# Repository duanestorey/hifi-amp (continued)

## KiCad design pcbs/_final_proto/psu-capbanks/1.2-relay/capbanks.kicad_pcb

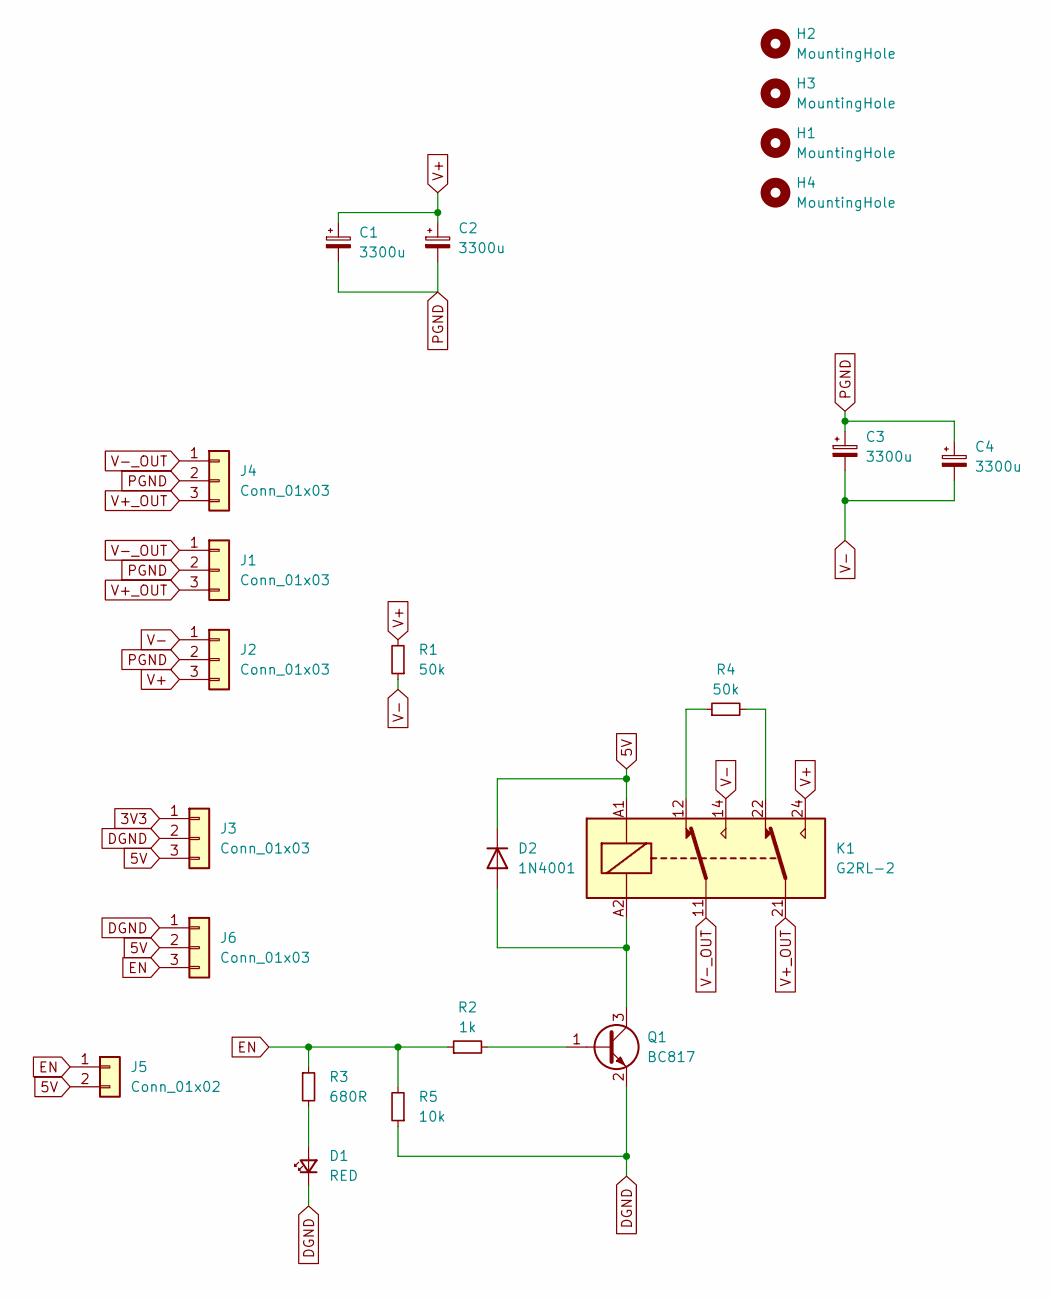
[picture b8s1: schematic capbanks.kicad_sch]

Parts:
C1, C2, C3, C4: 3300u; CP_Radial_D16.0mm_P7.50mm
D1: RED; LED_0805_2012Metric_Pad_HandSolder_Duane
D2: 1N4001; D_SMA
H1, H2, H3, H4: MountingHole; MountingHole_3.2mm_M3_DIN965_Pad_TopBottom
J1, J2, J4: Conn_01x03; JST_VH_B3P-VH-B_1x03_P3.96mm_Vertical_Duane
J3, J6: Conn_01x03; JST_PH_B3B-PH-K_1x03_P2.00mm_Vertical
J5: Conn_01x02; PinHeader_1x02_P2.54mm_Vertical
K1: G2RL-2; Relay_DPDT_Omron_G2RL-2
Q1: BC817; SOT-23
R1, R4: 50k; R_0805_2012Metric_Pad1.20x1.40mm_HandSolder_Duane
R2: 1k; R_0805_2012Metric_Pad1.20x1.40mm_HandSolder_Duane
R3: 680R; R_0805_2012Metric_Pad1.20x1.40mm_HandSolder_Duane
R5: 10k; R_0805_2012Metric_Pad1.20x1.40mm_HandSolder_Duane

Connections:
3V3: J3.1
5V: D2.1 (K), J3.3, J5.2, J6.2, K1.A1
DGND: D1.1 (K), J3.2, J6.1, Q1.2 (E), R5.1
EN: J5.1, J6.3, R2.1, R3.1, R5.2
unnamed: D1.2 (A), R3.2
unnamed: D2.2 (A), K1.A2, Q1.3 (C)
unnamed: K1.12, R4.1
unnamed: K1.22, R4.2
unnamed: Q1.1 (B), R2.2
PGND: C1.2, C2.2, C3.1, C4.1, J1.2, J2.2, J4.2
V+: C1.1, C2.1, J2.3, K1.24, R1.2
V+_OUT: J1.3, J4.3, K1.21
V-: C3.2, C4.2, J2.1, K1.14, R1.1
V-_OUT: J1.1, J4.1, K1.11

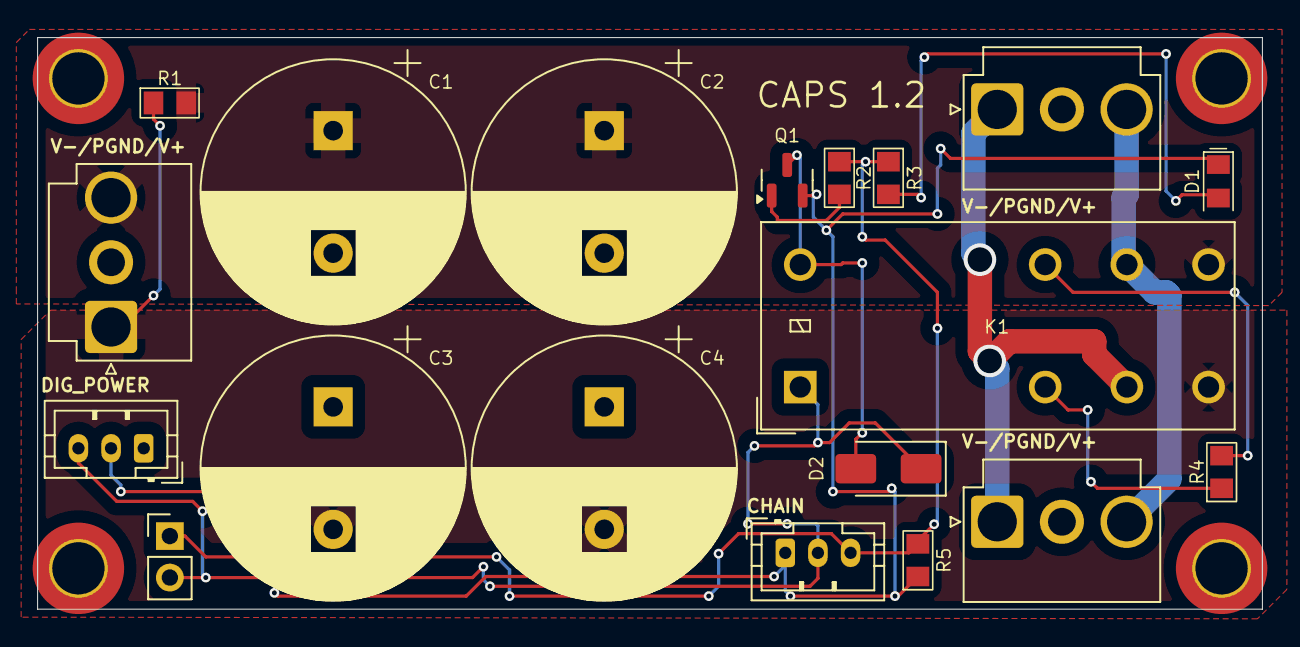
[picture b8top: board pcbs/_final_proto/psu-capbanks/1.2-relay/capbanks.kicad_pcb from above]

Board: 2 copper layers, 75.0 x 35.0 mm, 23 parts (0 on the bottom side), 13 nets.

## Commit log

2025-01-05 Adding submodules
2025-01-05 Adding license
2025-01-12 Create CNAME
2025-01-12 Fixes
2025-01-13 Display
2025-01-13 Adding
2025-01-13 Vinyl
2025-01-13 Adding dsp
2025-01-13 Cahnge for text
2025-01-13 Adding dual psu
2025-01-13 Updating extend
2025-01-13 Adding spdif
2025-01-13 input sel
2025-01-13 lm3886
2025-01-13 speciality
2025-01-13 Adding monoblock
2025-01-13 Updated specs
2025-01-13 Adding files
2025-01-13 Changing
2025-01-13 Adding LED info
2025-01-13 Updating specs
2025-01-13 ADding my link
2025-01-13 Updating LEDs
2025-01-13 PCBs
2025-01-13 Enclosures
2025-01-13 Adding software
2025-01-13 Adding docs
2025-01-13 Adding pcbs and kicad
2025-01-13 Adding soic
2025-01-13 Cables
2025-01-13 Build
2025-01-13 Adding build info
2025-01-13 Organzing
2025-01-13 Changing links
2025-01-13 Updating
2025-01-13 updaties
2025-01-13 Ground lift
2025-01-15 Adding image
2025-01-16 Moving PCBs
2025-02-14 Major updates
2025-02-15 Updating docs
2025-02-15 Updating log
2025-02-15 Format
2025-02-15 Updating pin outs
2025-02-15 Updated docs
2025-02-15 Fixing small issues with input selector
2025-02-17 More updates
2025-02-18 Updating connectors
2025-02-21 Updating code and designs
2025-02-23 Updatined code
2025-03-21 Staging
2025-05-14 First pass of bluetooth LE
2025-10-22 All changes
2025-11-16 Working code
2025-11-16 Looking good
